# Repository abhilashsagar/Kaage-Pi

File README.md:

# Kaage-Pi

Why I Built It
I wanted to see if a usable Linux single-board computer could be built in India for under ₹2,000, using nothing more than open components, community knowledge, and hand-soldering tools.

Most of the SBCs we use today — Raspberry Pi, BeagleBone, etc. — are amazing. I wanted to prove that we can build our own — from the ground up — using parts available locally, and learn how Linux truly runs on bare metal in the process.

That’s how Kaage Pi was born: a home-soldered board built around the Allwinner V3s, an ARM Cortex-A7 SoC with 64 MB of integrated DDR2 RAM — powerful enough to boot Linux without any external memory.

This project isn’t about competing with Raspberry Pi. It’s about understanding, experimenting, and inspiring others to start their own journey in open hardware — where you can hold a running Linux system that you built with your own hands.

If you’ve ever wondered “Can I really make my own Linux board?” — the answer is yes, you can. Start small, stay patient, and let curiosity lead.

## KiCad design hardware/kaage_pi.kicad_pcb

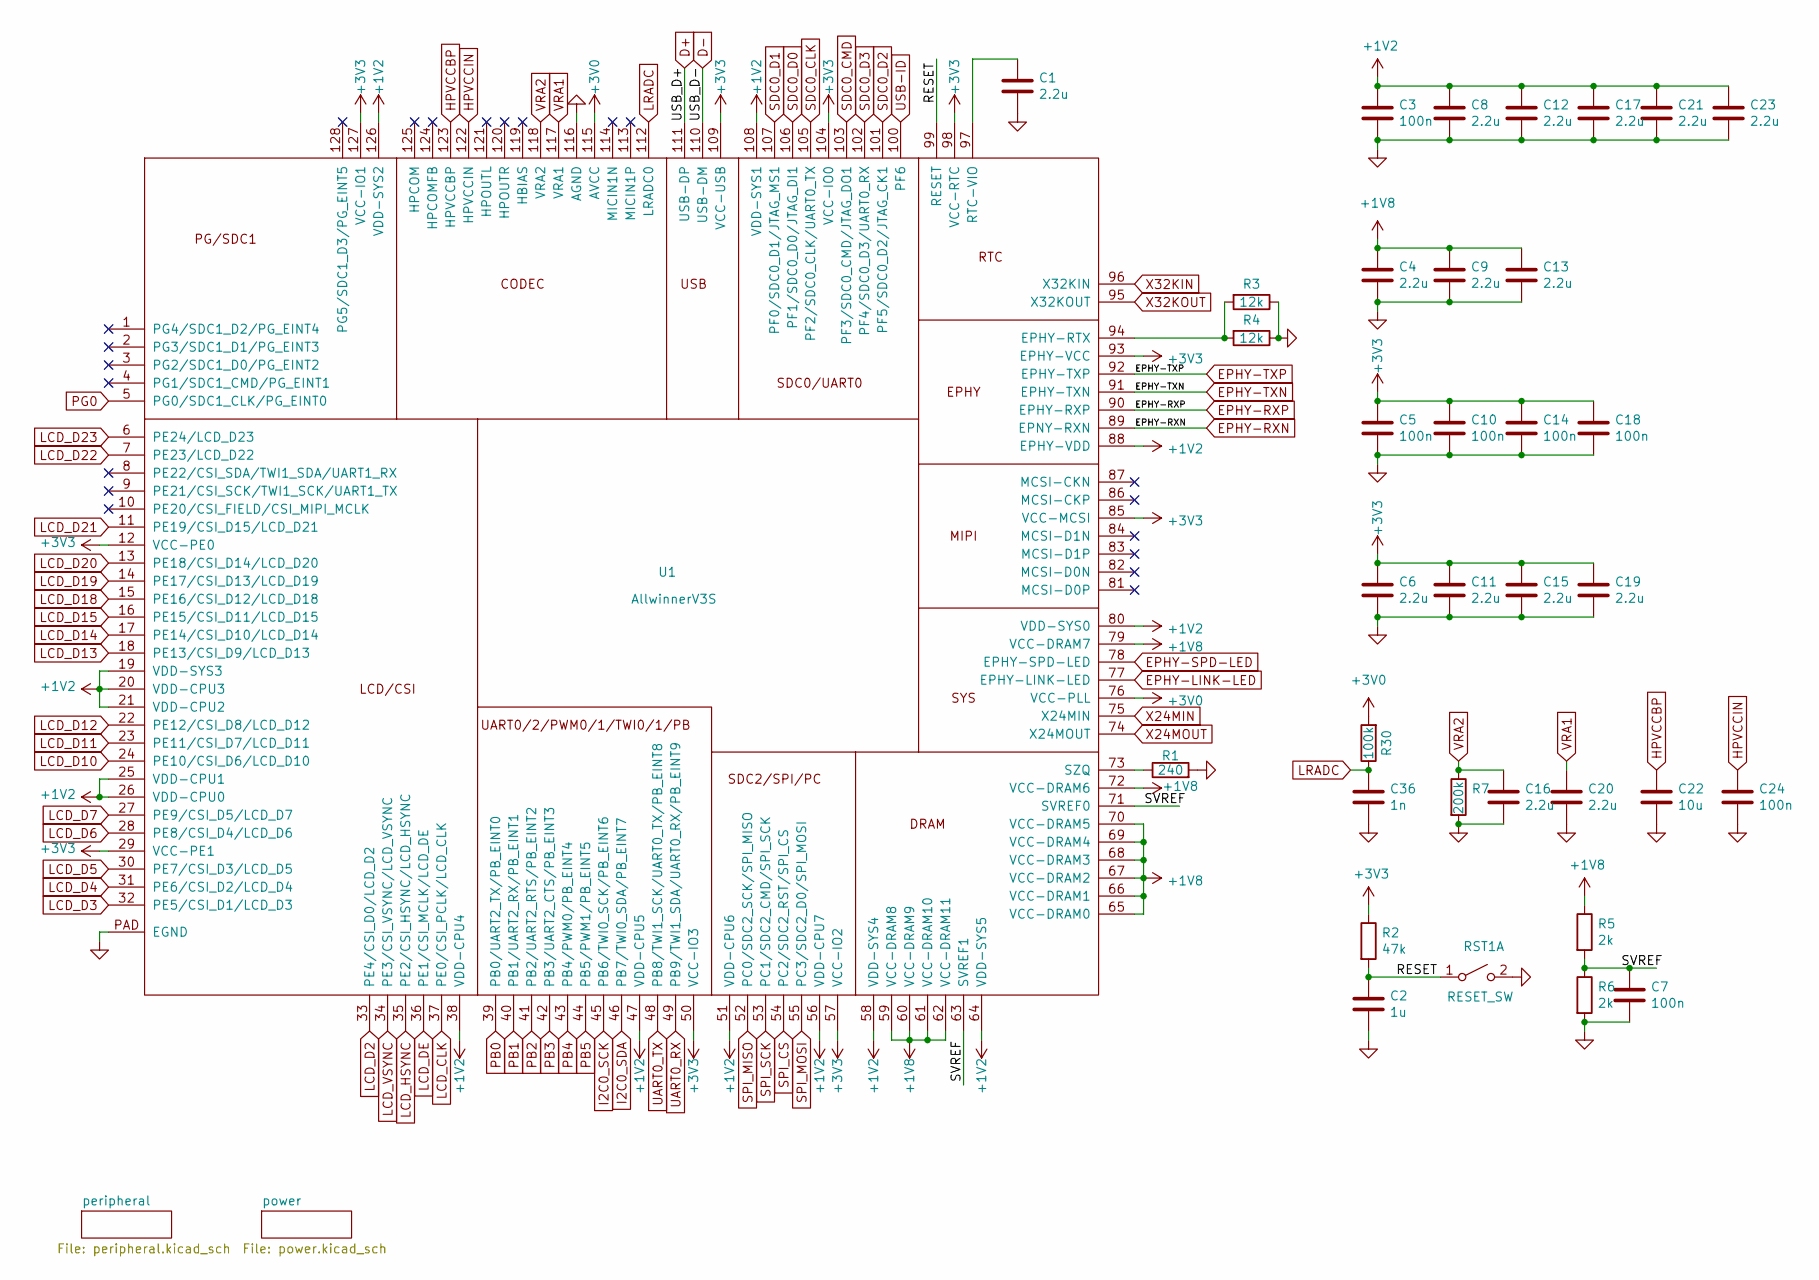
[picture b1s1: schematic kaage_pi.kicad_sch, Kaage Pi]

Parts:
C1, C4, C6, C8, C9, C11, C12, C13, C15, C16, C17, C19, C20, C21, C23: 2.2u; C_0805_2012Metric
C2: 1u; C_0603_1608Metric
C3, C5, C7, C10, C14, C18, C24: 100n; C_0603_1608Metric
C22: 10u; C_0603_1608Metric
C36: 1n; C_0603_1608Metric
R1: 240; R_0603_1608Metric
R2: 47k; R_0603_1608Metric
R3, R4: 12k; R_0603_1608Metric
R5, R6: 2k; R_0603_1608Metric
R7: 200k; R_0603_1608Metric
R30: 100k; R_0603_1608Metric
RST1: RESET_SW; SW_Tactile_SPST_NO_Straight_CK_PTS636Sx25SMTRLFS
U1: AllwinnerV3S; eLQFP-128_14x14mm_P0.4mm

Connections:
+1V2: C3.1, C8.1, C12.1, C17.1, C21.1, C23.1, U1.19 (VDD-SYS3), U1.20 (VDD-CPU3), U1.21 (VDD-CPU2), U1.25 (VDD-CPU1), U1.26 (VDD-CPU0), U1.38 (VDD-CPU4), U1.47 (VDD-CPU5), U1.51 (VDD-CPU6), U1.56 (VDD-CPU7), U1.58 (VDD-SYS4), U1.64 (VDD-SYS5), U1.80 (VDD-SYS0), U1.88 (EPHY-VDD), U1.108 (VDD-SYS1), U1.126 (VDD-SYS2); also elsewhere on the board
+1V8: C4.1, C9.1, C13.1, R5.1, U1.59 (VCC-DRAM8), U1.60 (VCC-DRAM9), U1.61 (VCC-DRAM10), U1.62 (VCC-DRAM11), U1.65 (VCC-DRAM0), U1.66 (VCC-DRAM1), U1.67 (VCC-DRAM2), U1.68 (VCC-DRAM3), U1.69 (VCC-DRAM4), U1.70 (VCC-DRAM5), U1.72 (VCC-DRAM6), U1.79 (VCC-DRAM7); also elsewhere on the board
+3V0: R30.2, U1.76 (VCC-PLL), U1.115 (AVCC); also elsewhere on the board
+3V3: C5.1, C6.1, C10.1, C11.1, C14.1, C15.1, C18.1, C19.1, R2.1, U1.12 (VCC-PE0), U1.29 (VCC-PE1), U1.50 (VCC-IO3), U1.57 (VCC-IO2), U1.85 (VCC-MCSI), U1.93 (EPHY-VCC), U1.98 (VCC-RTC), U1.104 (VCC-IO0), U1.109 (VCC-USB), U1.127 (VCC-IO1); also elsewhere on the board
/RESET: C2.1, R2.2, RST1.1 (A), U1.99 (RESET)
/SVREF: C7.1, R5.2, R6.1, U1.63 (SVREF1), U1.71 (SVREF0)
D+: U1.111 (USB-DP); also elsewhere on the board
D-: U1.110 (USB-DM); also elsewhere on the board
EPHY-LINK-LED: U1.77 (EPHY-LINK-LED); also elsewhere on the board
EPHY-RXN: U1.89 (EPNY-RXN); also elsewhere on the board
EPHY-RXP: U1.90 (EPHY-RXP); also elsewhere on the board
EPHY-SPD-LED: U1.78 (EPHY-SPD-LED); also elsewhere on the board
EPHY-TXN: U1.91 (EPHY-TXN); also elsewhere on the board
EPHY-TXP: U1.92 (EPHY-TXP); also elsewhere on the board
GND: C1.2, C2.2, C3.2, C4.2, C5.2, C6.2, C7.2, C8.2, C9.2, C10.2, C11.2, C12.2, C13.2, C14.2, C15.2, C16.2, C17.2, C18.2, C19.2, C20.2, C21.2, C22.2, C23.2, C24.2, C36.2, R1.2, R3.1, R4.1, R6.2, R7.2, RST1.2 (B), U1.116 (AGND), U1.PAD (EGND); also elsewhere on the board
HPVCCBP: C22.1, U1.123 (HPVCCBP)
HPVCCIN: C24.1, U1.122 (HPVCCIN)
I2C0_SCK: U1.45 (PB6/TWI0_SCK/PB_EINT6); also elsewhere on the board
I2C0_SDA: U1.46 (PB7/TWI0_SDA/PB_EINT7); also elsewhere on the board
LCD_CLK: U1.37 (PE0/CSI_PCLK/LCD_CLK); also elsewhere on the board
LCD_D2: U1.33 (PE4/CSI_D0/LCD_D2); also elsewhere on the board
LCD_D3: U1.32 (PE5/CSI_D1/LCD_D3); also elsewhere on the board
LCD_D4: U1.31 (PE6/CSI_D2/LCD_D4); also elsewhere on the board
LCD_D5: U1.30 (PE7/CSI_D3/LCD_D5); also elsewhere on the board
LCD_D6: U1.28 (PE8/CSI_D4/LCD_D6); also elsewhere on the board
LCD_D7: U1.27 (PE9/CSI_D5/LCD_D7); also elsewhere on the board
LCD_D10: U1.24 (PE10/CSI_D6/LCD_D10); also elsewhere on the board
LCD_D11: U1.23 (PE11/CSI_D7/LCD_D11); also elsewhere on the board
LCD_D12: U1.22 (PE12/CSI_D8/LCD_D12); also elsewhere on the board
LCD_D13: U1.18 (PE13/CSI_D9/LCD_D13); also elsewhere on the board
LCD_D14: U1.17 (PE14/CSI_D10/LCD_D14); also elsewhere on the board
LCD_D15: U1.16 (PE15/CSI_D11/LCD_D15); also elsewhere on the board
LCD_D18: U1.15 (PE16/CSI_D12/LCD_D18); also elsewhere on the board
LCD_D19: U1.14 (PE17/CSI_D13/LCD_D19); also elsewhere on the board
LCD_D20: U1.13 (PE18/CSI_D14/LCD_D20); also elsewhere on the board
LCD_D21: U1.11 (PE19/CSI_D15/LCD_D21); also elsewhere on the board
LCD_D22: U1.7 (PE23/LCD_D22); also elsewhere on the board
LCD_D23: U1.6 (PE24/LCD_D23); also elsewhere on the board
LCD_DE: U1.36 (PE1/CSI_MCLK/LCD_DE); also elsewhere on the board
LCD_HSYNC: U1.35 (PE2/CSI_HSYNC/LCD_HSYNC); also elsewhere on the board
LCD_VSYNC: U1.34 (PE3/CSI_VSYNC/LCD_VSYNC); also elsewhere on the board
LRADC: C36.1, R30.1, U1.112 (LRADC0)
unnamed: R3.2, R4.2, U1.94 (EPHY-RTX)
unnamed: C1.1, U1.97 (RTC-VIO)
unnamed: R1.1, U1.73 (SZQ)
PB0: U1.39 (PB0/UART2_TX/PB_EINT0); also elsewhere on the board
PB1: U1.40 (PB1/UART2_RX/PB_EINT1); also elsewhere on the board
PB2: U1.41 (PB2/UART2_RTS/PB_EINT2); also elsewhere on the board
PB3: U1.42 (PB3/UART2_CTS/PB_EINT3); also elsewhere on the board
PB4: U1.43 (PB4/PWM0/PB_EINT4); also elsewhere on the board
PB5: U1.44 (PB5/PWM1/PB_EINT5); also elsewhere on the board
PG0: U1.5 (PG0/SDC1_CLK/PG_EINT0); also elsewhere on the board
SDC0_CLK: U1.105 (PF2/SDC0_CLK/UART0_TX); also elsewhere on the board
SDC0_CMD: U1.103 (PF3/SDC0_CMD/JTAG_DO1); also elsewhere on the board
SDC0_D0: U1.106 (PF1/SDC0_D0/JTAG_DI1); also elsewhere on the board
SDC0_D1: U1.107 (PF0/SDC0_D1/JTAG_MS1); also elsewhere on the board
SDC0_D2: U1.101 (PF5/SDC0_D2/JTAG_CK1); also elsewhere on the board
SDC0_D3: U1.102 (PF4/SDC0_D3/UART0_RX); also elsewhere on the board
SPI_CS: U1.54 (PC2/SDC2_RST/SPI_CS); also elsewhere on the board
SPI_MISO: U1.52 (PC0/SDC2_SCK/SPI_MISO); also elsewhere on the board
SPI_MOSI: U1.55 (PC3/SDC2_D0/SPI_MOSI); also elsewhere on the board
SPI_SCK: U1.53 (PC1/SDC2_CMD/SPI_SCK); also elsewhere on the board
UART0_RX: U1.49 (PB9/TWI1_SDA/UART0_RX/PB_EINT9); also elsewhere on the board
UART0_TX: U1.48 (PB8/TWI1_SCK/UART0_TX/PB_EINT8); also elsewhere on the board
USB-ID: U1.100 (PF6); also elsewhere on the board
VRA1: C20.1, U1.117 (VRA1)
VRA2: C16.1, R7.1, U1.118 (VRA2)
X24MIN: U1.75 (X24MIN); also elsewhere on the board
X24MOUT: U1.74 (X24MOUT); also elsewhere on the board
X32KIN: U1.96 (X32KIN); also elsewhere on the board
X32KOUT: U1.95 (X32KOUT); also elsewhere on the board

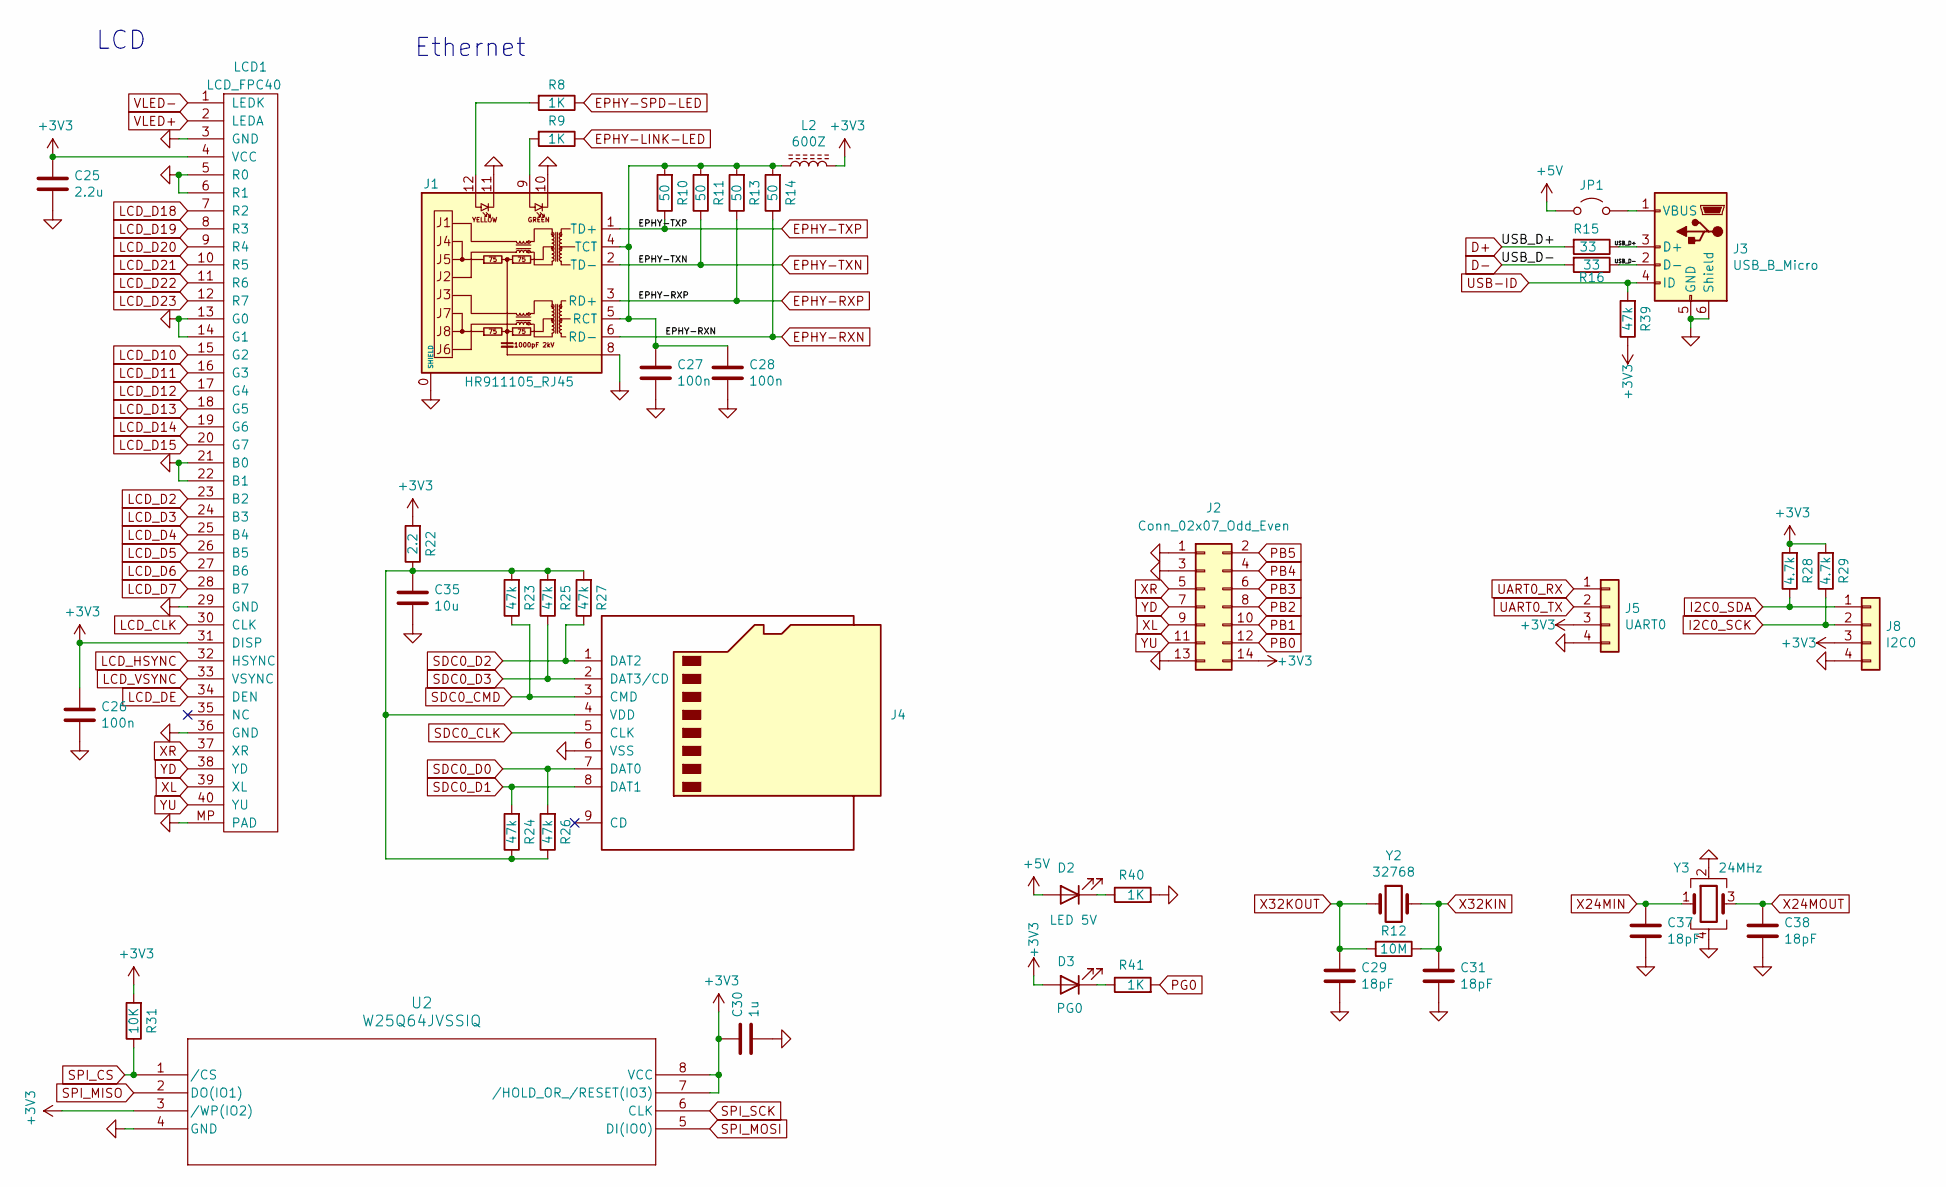
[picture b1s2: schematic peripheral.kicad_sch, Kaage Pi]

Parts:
C25: 2.2u; C_0805_2012Metric
C26, C27, C28: 100n; C_0603_1608Metric
C29, C31, C37, C38: 18pF; C_0603_1608Metric
C30: 1u; C_0603_1608Metric
C35: 10u; C_0805_2012Metric
D2: LED 5V; LED_0603_1608Metric_Pad1.05x0.95mm_HandSolder
D3: PG0; LED_0603_1608Metric_Pad1.05x0.95mm_HandSolder
J1: HR911105_RJ45
J2: Conn_02x07_Odd_Even; PinSocket_2x07_P2.54mm_Vertical
J3: USB_B_Micro; USB_Micro-B_Molex-105017-0001
J4: Micro_SD_Card_Ebay; micro_sd_card
J5: UART0; PinSocket_1x04_P2.00mm_Vertical
J8: I2C0; PinSocket_1x04_P2.00mm_Vertical
JP1: Jumper_2_Open; PinHeader_1x02_P2.54mm_Vertical
L2: 600Z; L_0603_1608Metric
LCD1: LCD_FPC40; Hirose_FH12-40S-0.5SH_1x40-1MP_P0.50mm_Horizontal
R8, R9, R40, R41: 1K; R_0603_1608Metric
R10, R11, R13, R14: 50; R_0603_1608Metric
R12: 10M; R_0805_2012Metric
R15, R16: 33; R_0603_1608Metric
R22: 2.2; R_0603_1608Metric
R23, R24, R25, R26, R27, R39: 47k; R_0603_1608Metric
R28, R29: 4.7k; R_0603_1608Metric
R31: 10K; R_0603_1608Metric
U2: W25Q64JVSSIQ; SOIC-8_5.23x5.23mm_P1.27mm
Y2: 32768; Crystal_C26-LF_D2.1mm_L6.5mm_Horizontal
Y3: 24MHz; Crystal_SMD_3225-4Pin_3.2x2.5mm

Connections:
+3V3: C25.1, C26.1, C30.1, D3.2 (A), J2.14, J5.3, J8.3, L2.2, LCD1.4 (VCC), LCD1.31 (DISP), R22.2, R28.2, R29.2, R31.2, R39.1, U2.3 (/WP(IO2)), U2.7 (/HOLD_OR_/RESET(IO3)), U2.8 (VCC); also elsewhere on the board
+5V: D2.2 (A), JP1.1 (A); also elsewhere on the board
D+: J3.3 (D+), R15.1, R15.2; also elsewhere on the board
D-: J3.2 (D-), R16.1, R16.2; also elsewhere on the board
EPHY-LINK-LED: R9.1; also elsewhere on the board
EPHY-RXN: J1.6 (RD-), R14.1; also elsewhere on the board
EPHY-RXP: J1.3 (RD+), R13.1; also elsewhere on the board
EPHY-SPD-LED: R8.1; also elsewhere on the board
EPHY-TXN: J1.2 (TD-), R11.1; also elsewhere on the board
EPHY-TXP: J1.1 (TD+), R10.1; also elsewhere on the board
GND: C25.2, C26.2, C27.2, C28.2, C29.2, C30.2, C31.2, C35.2, C37.2, C38.2, J1.0 (SHIELD), J1.8, J1.10, J1.11, J2.1, J2.3, J2.13, J3.5 (GND), J3.6 (Shield), J4.6 (VSS), J5.4, J8.4, LCD1.3 (GND), LCD1.5 (R0), LCD1.6 (R1), LCD1.13 (G0), LCD1.14 (G1), LCD1.21 (B0), LCD1.22 (B1), LCD1.29 (GND), LCD1.36 (GND), LCD1.MP (PAD), R40.2, U2.4 (GND), Y3.2, Y3.4; also elsewhere on the board
I2C0_SCK: J8.2, R29.1; also elsewhere on the board
I2C0_SDA: J8.1, R28.1; also elsewhere on the board
LCD_CLK: LCD1.30 (CLK); also elsewhere on the board
LCD_D2: LCD1.23 (B2); also elsewhere on the board
LCD_D3: LCD1.24 (B3); also elsewhere on the board
LCD_D4: LCD1.25 (B4); also elsewhere on the board
LCD_D5: LCD1.26 (B5); also elsewhere on the board
LCD_D6: LCD1.27 (B6); also elsewhere on the board
LCD_D7: LCD1.28 (B7); also elsewhere on the board
LCD_D10: LCD1.15 (G2); also elsewhere on the board
LCD_D11: LCD1.16 (G3); also elsewhere on the board
LCD_D12: LCD1.17 (G4); also elsewhere on the board
LCD_D13: LCD1.18 (G5); also elsewhere on the board
LCD_D14: LCD1.19 (G6); also elsewhere on the board
LCD_D15: LCD1.20 (G7); also elsewhere on the board
LCD_D18: LCD1.7 (R2); also elsewhere on the board
LCD_D19: LCD1.8 (R3); also elsewhere on the board
LCD_D20: LCD1.9 (R4); also elsewhere on the board
LCD_D21: LCD1.10 (R5); also elsewhere on the board
LCD_D22: LCD1.11 (R6); also elsewhere on the board
LCD_D23: LCD1.12 (R7); also elsewhere on the board
LCD_DE: LCD1.34 (DEN); also elsewhere on the board
LCD_HSYNC: LCD1.32 (HSYNC); also elsewhere on the board
LCD_VSYNC: LCD1.33 (VSYNC); also elsewhere on the board
unnamed: D2.1 (K), R40.1
unnamed: D3.1 (K), R41.1
unnamed: J1.9, R9.2
unnamed: J1.12, R8.2
unnamed: C27.1, C28.1, J1.4 (TCT), J1.5 (RCT), L2.1, R10.2, R11.2, R13.2, R14.2
unnamed: J3.1 (VBUS), JP1.2 (B)
unnamed: C35.1, J4.4 (VDD), R22.1, R23.2, R24.1, R25.2, R26.1, R27.2
PB0: J2.12; also elsewhere on the board
PB1: J2.10; also elsewhere on the board
PB2: J2.8; also elsewhere on the board
PB3: J2.6; also elsewhere on the board
PB4: J2.4; also elsewhere on the board
PB5: J2.2; also elsewhere on the board
PG0: R41.2; also elsewhere on the board
SDC0_CLK: J4.5 (CLK); also elsewhere on the board
SDC0_CMD: J4.3 (CMD), R23.1; also elsewhere on the board
SDC0_D0: J4.7 (DAT0), R26.2; also elsewhere on the board
SDC0_D1: J4.8 (DAT1), R24.2; also elsewhere on the board
SDC0_D2: J4.1 (DAT2), R27.1; also elsewhere on the board
SDC0_D3: J4.2 (DAT3/CD), R25.1; also elsewhere on the board
SPI_CS: R31.1, U2.1 (/CS); also elsewhere on the board
SPI_MISO: U2.2 (DO(IO1)); also elsewhere on the board
SPI_MOSI: U2.5 (DI(IO0)); also elsewhere on the board
SPI_SCK: U2.6 (CLK); also elsewhere on the board
UART0_RX: J5.1; also elsewhere on the board
UART0_TX: J5.2; also elsewhere on the board
USB-ID: J3.4 (ID), R39.2; also elsewhere on the board
VLED+: LCD1.2 (LEDA); also elsewhere on the board
VLED-: LCD1.1 (LEDK); also elsewhere on the board
X24MIN: C37.1, Y3.1; also elsewhere on the board
X24MOUT: C38.1, Y3.3; also elsewhere on the board
X32KIN: C31.1, R12.1, Y2.2; also elsewhere on the board
X32KOUT: C29.1, R12.2, Y2.1; also elsewhere on the board
XL: J2.9, LCD1.39 (XL)
XR: J2.5, LCD1.37 (XR)
YD: J2.7, LCD1.38 (YD)
YU: J2.11, LCD1.40 (YU)

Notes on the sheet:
LCD
Ethernet

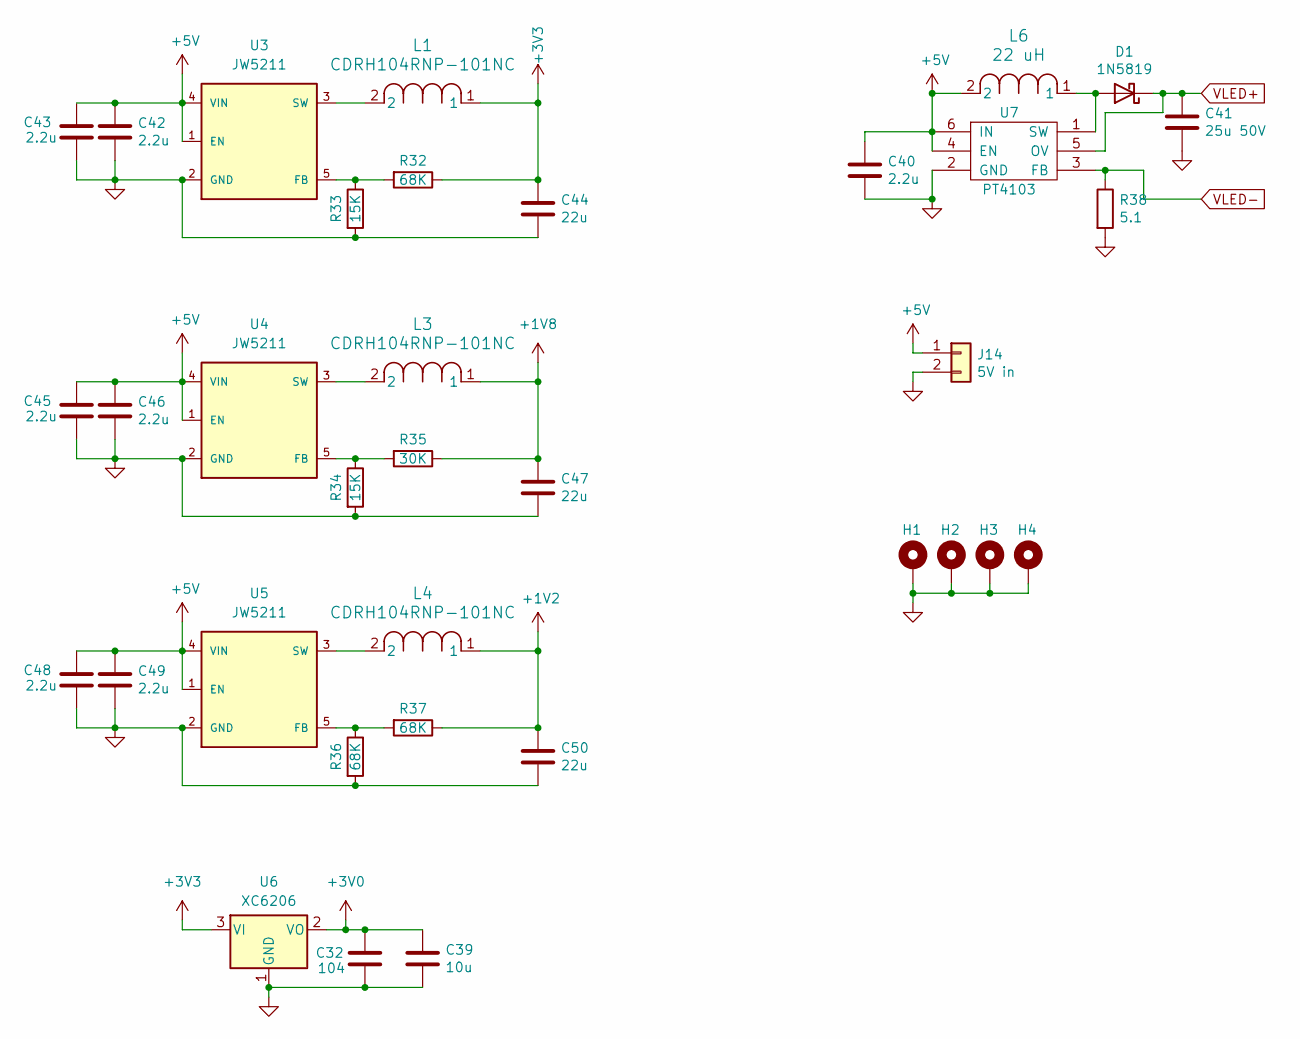
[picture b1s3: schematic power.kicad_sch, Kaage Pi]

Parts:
C32: 104; C_0603_1608Metric
C39: 10u; C_0603_1608Metric
C40, C42, C43, C45, C46, C48, C49: 2.2u; C_0805_2012Metric
C41: 25u 50V; C_1206_3216Metric
C44, C47, C50: 22u; C_0603_1608Metric
D1: 1N5819; D_SOD-123
H1, H2, H3, H4: MountingHole_Pad; MountingHole_2.5mm_Pad
J14: 5V in; PinSocket_1x02_P2.54mm_Vertical
L1, L3, L4: CDRH104RNP-101NC; SWPA6045S220MT
L6: 22 uH; SWPA6045S220MT
R32, R36, R37: 68K; R_0603_1608Metric
R33, R34: 15K; R_0603_1608Metric
R35: 30K; R_0603_1608Metric
R38: 5.1; R_0603_1608Metric
U3, U4, U5: JW5211; SOT-23-5
U6: XC6206; SOT-23-3
U7: PT4103; SOT-23-6

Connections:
+1V2: C50.1, L4.1, R37.1; also elsewhere on the board
+1V8: C47.1, L3.1, R35.1; also elsewhere on the board
+3V0: C32.1, C39.1, U6.2 (VO); also elsewhere on the board
+3V3: C44.1, L1.1, R32.1, U6.3 (VI); also elsewhere on the board
+5V: C40.1, C42.1, C43.1, C45.1, C46.1, C48.1, C49.1, J14.1, L6.2, U3.1 (EN), U3.4 (VIN), U4.1 (EN), U4.4 (VIN), U5.1 (EN), U5.4 (VIN), U7.4 (EN), U7.6 (IN); also elsewhere on the board
GND: C32.2, C39.2, C40.2, C41.2, C42.2, C43.2, C44.2, C45.2, C46.2, C47.2, C48.2, C49.2, C50.2, H1.1, H2.1, H3.1, H4.1, J14.2, R33.2, R34.2, R36.2, R38.2, U3.2 (GND), U4.2 (GND), U5.2 (GND), U6.1 (GND), U7.2 (GND); also elsewhere on the board
unnamed: D1.2 (A), L6.1, U7.1 (SW)
unnamed: R32.2, R33.1, U3.5 (FB)
unnamed: L1.2, U3.3 (SW)
unnamed: R34.1, R35.2, U4.5 (FB)
unnamed: L3.2, U4.3 (SW)
unnamed: R36.1, R37.2, U5.5 (FB)
unnamed: L4.2, U5.3 (SW)
VLED+: C41.1, D1.1 (K), U7.5 (OV); also elsewhere on the board
VLED-: R38.1, U7.3 (FB); also elsewhere on the board

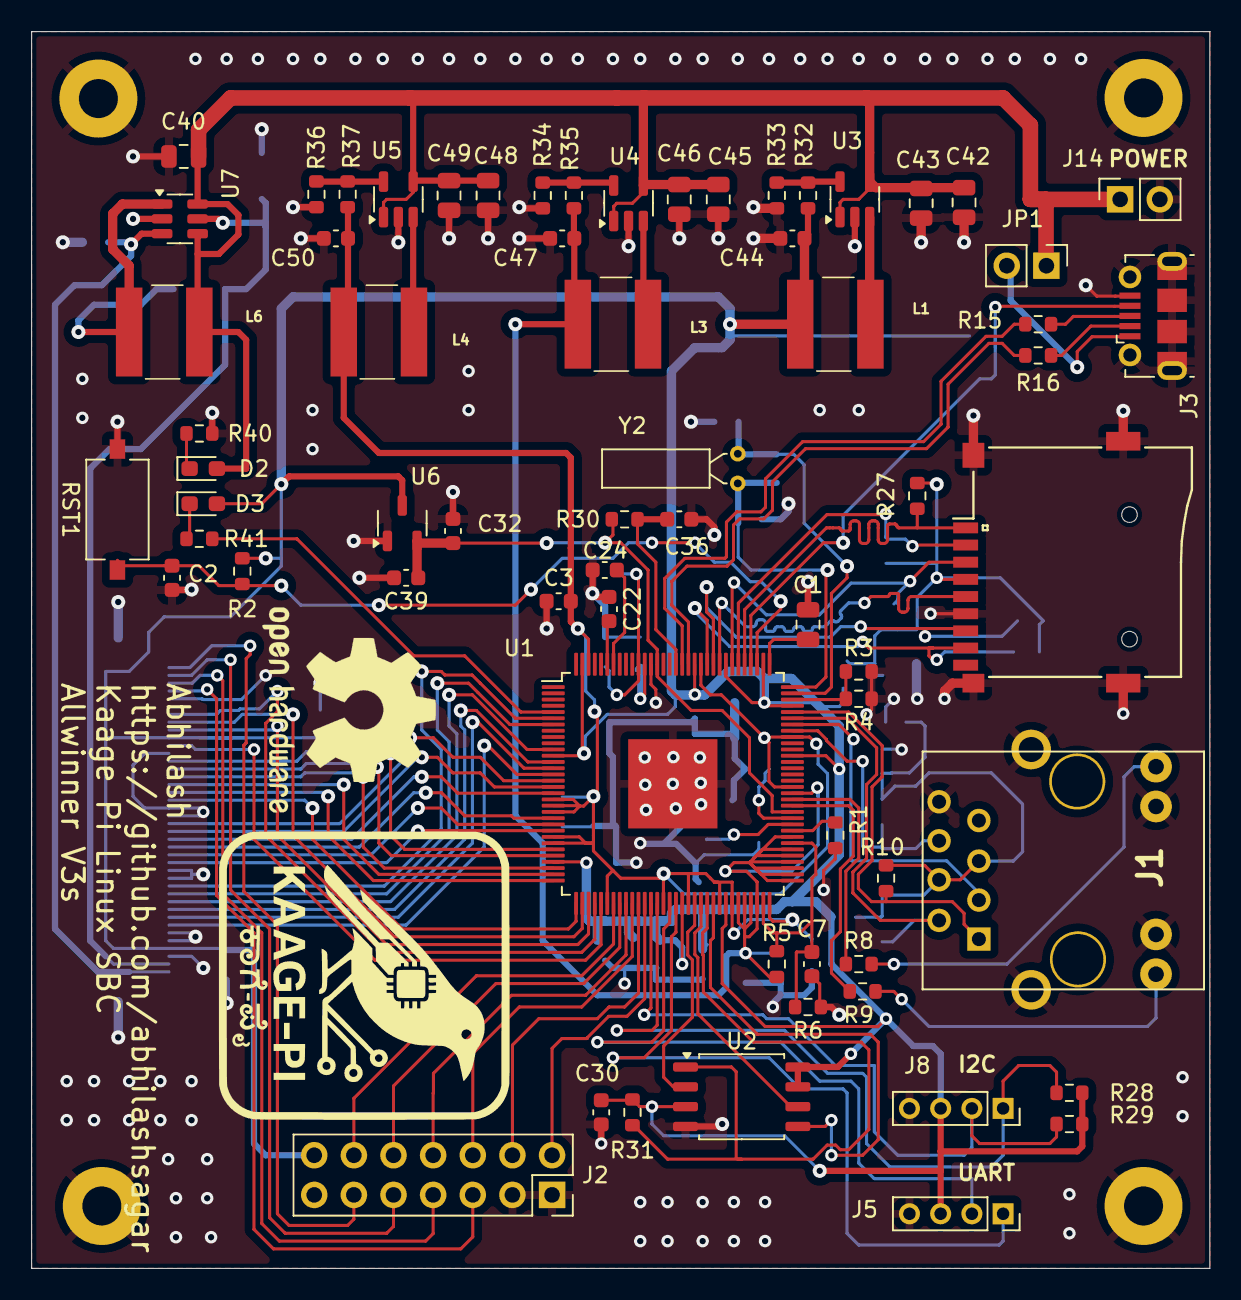
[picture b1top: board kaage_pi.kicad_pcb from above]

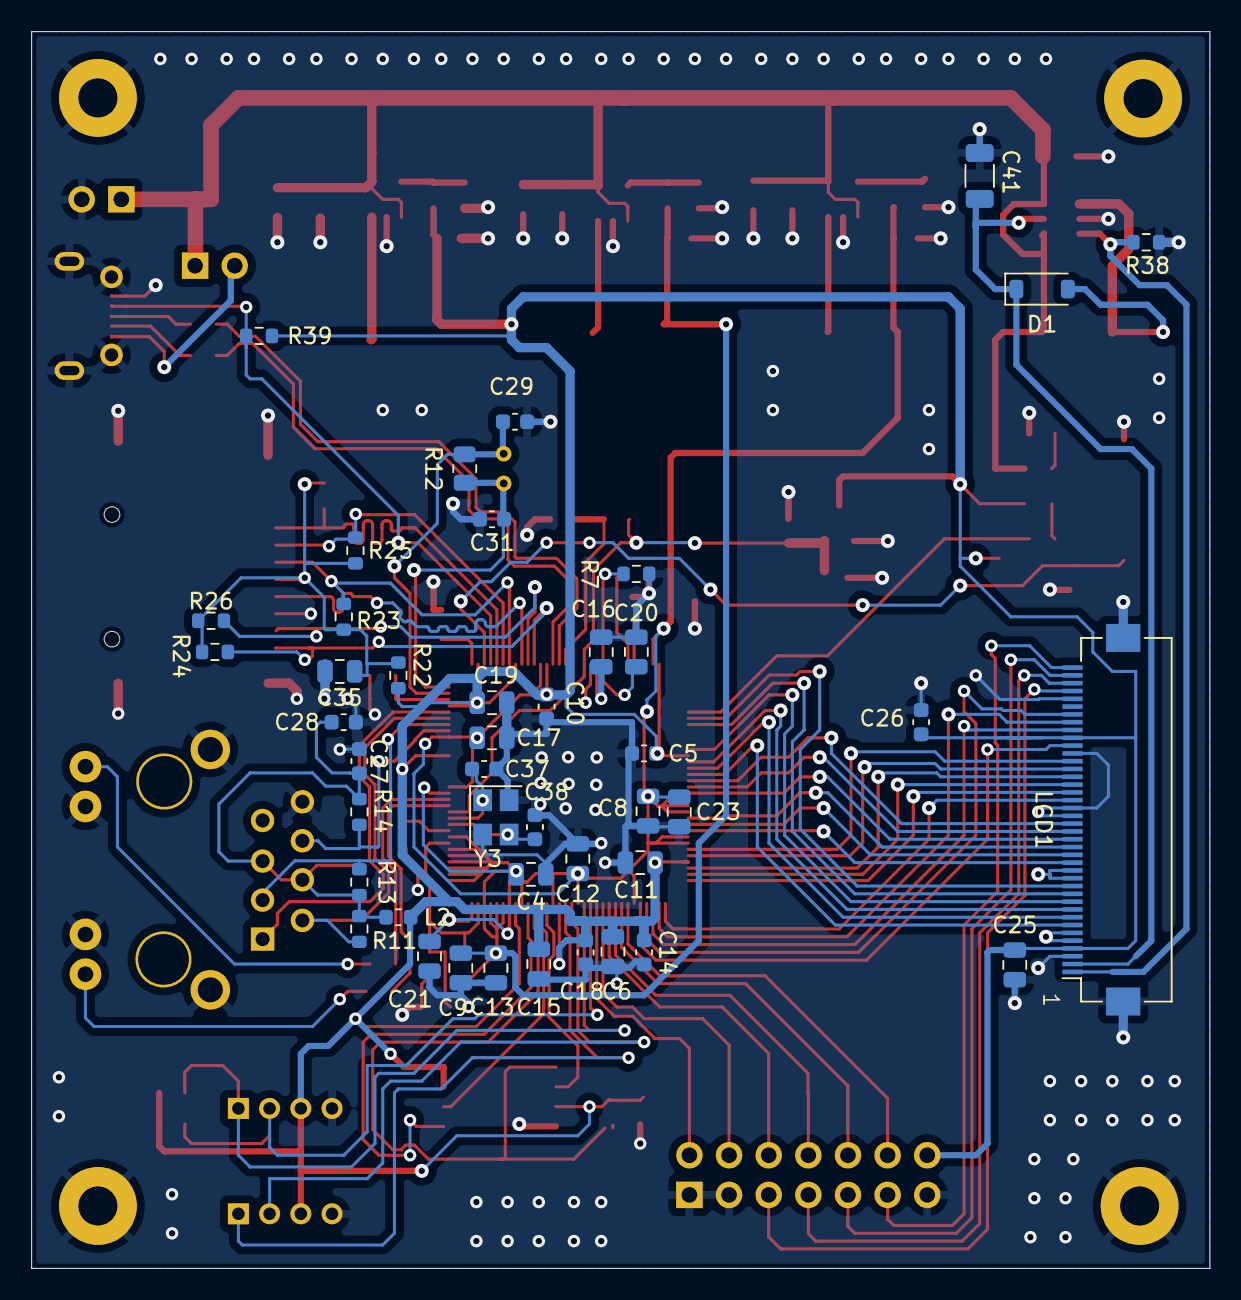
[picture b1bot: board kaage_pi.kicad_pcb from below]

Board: 4 copper layers, 75.5 x 79.2 mm, 115 parts (44 on the bottom side), 92 nets.

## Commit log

2025-10-25 folder struct
2025-10-25 Kicad files
2025-10-25 add folder struct
